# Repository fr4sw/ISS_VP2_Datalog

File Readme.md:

# ISS\_VP2\_Datalog

# Readme

Version : 0.1.6c Date : 2026-08-13

Rédacteur : Rémi Chapdelaine

# 1. Objectif du projet

Le projet ISS\_VP2\_Datalog a pour but de fournir un datalogger externe aux stations Davis Vantage Pro2 ET transmettre les informations par un lien meshtastic (ou tout autre modem série).

Ce projet a vocation a utiliser directement l'ISS (ensemble de capteurs) sans nécessiter la console et le module datalogger de Davis, permettant des économies.

L'horodatage fiable fait partie des principes important pour pouvoir recoller les informations des différentes stations.

La normalisation des unités et des mesures doit viser les bonnes pratiques en météorologie, dans les limites de ce qui est fourni par Davis.
## 1A. Etat actuel (13/8/2026 v0.1.6c)

En cours de mise au point, fonctionnel avec ISS filaire (seul temp et Hum testés), nRF52840-Xiao, BME680, RTC DS3231, GPS, carte µSD.
Certains paramétrage peuvent s'effectuer depuis le moniteur série (serial).
Sur la carte SD on écrit toutes les 30s (paramétrable) dans un fichier .csv; toutes les 5 minutes (paramétrable) on fait la synthèse (comme le fait WeeWx/Davis...) et on enregistre aussi (c'est cela qu'on enverra).

On écrit aussi un EVENTS.log qui récapitule les évènements principaux (dont les durée d'allumage GPS et les décalages horaires - permettront d'estimer la possibilité d'allonger la durée de recalage).

Meshtastic en protobuff simplifié est globalement validé, les infos remontent, tests à poursuivre.

En cours : automatisation du capteur I2C interne pour supporter/reconaitre automatiquement BME680, BME280, BMP280 ...

# 2. Contexte
Ce projet a été utilisé plusieurs années comme projet de fin d'étude en BTS Systèmes numériques/CIEL Electronique en partenariat avec l'association MeteoR-OI.

# 3. Pré-requis - versions
Testé :
IDE/Core : Arduino IDE portable 1.8.19, core Seed nRF52 Boards 1.1.13, core ESP32 3.2.0-\>3.3.11 (Wire et SD sont utilisés mais elles sont incluses dans les Cores)
Librairies : 
- BME680 Adafruit (2.0.6) (Adafruit BusIO 1.17.4, Adafruit unified sensors 1.1.15) https://github.com/adafruit/Adafruit_BME680
- RTClib Adafruit (2.1.4) https://github.com/adafruit/RTClib
- TinyGPSplus mikalhart (1.0.3) (utile seulement si GPS - Cf config/boardConfig) https://github.com/mikalhart/TinyGPSPlus

# 4. Matériel Davis

Ce projet est conçu pour récupérer les informations d'une ensemble de capteurs ISS Davis Vantage Pro2 qui existe sous 2 formes :

- filaire= liaison RS485, alimentation par le fil

- sans fil = liaison radio en modulation FSK, fréquence selon les normes locales ISM (868, 915, 433 MHz)

## 4A. Documentations
- Wiki du projet DavisRFM69, décrit les trames entre ISS et console : https://github.com/dekay/DavisRFM69/wiki/Message-Protocol
- Documentation Davis de la communication avec le Datalogger (weatherlink) : https://support.davisinstruments.com/article/rbzgl0rh6k-vantage-pro-pro-2-and-vue-communications-reference-2-6-1-any-os pointe vers https://cdn.shopify.com/s/files/1/0515/5992/3873/files/VantageSerialProtocolDocs_v261.pdf?v=1614399559
  
- Meteoengins décrit la méthode d'enregistrement dans Weatherlink et datalogger ainsi que les calculs de données dérivées (indice de chaleur, point de rosée, évapotranspiration, ...) : http://meteoengins.fr/documents/davis/Davis_Data_Archived_v3.pdf

# 5. Matériel

Des cartes spécifiques ont été conçues par les étudiants de BTS durant les projets ou par l'enseignant, cf rubrique Hardware.

Le logiciel utilisé est Kicad 9.

# 6. Logiciel

Le logiciel est structuré pour permettre :

- des développements partagés (modules par fonction)

- une maintenance facile (commentaires, documentation)

- un développement sur des matériels différents (couches d'abstraction, définitions des cartes et pins centralisées)

- Arduino 1.8.19 portable ou PlatformIO, les 2 peuvent etre utilisés

Les développements doivent respecter les règles de codage (cf doc) et etre accessible à des BTS.  
Chaque ligne de code doit pouvoir être expliquée à un étudiant de BTS.  
Si une ligne nécessite une longue explication, elle doit être réécrite de manière plus explicite.

Une partie du développement a été réalisé avec l'aide de Claude Sonnet 5, en corrigeant ses erreurs et affinant les possibiités.

Les règles de codages sont dans le document CodingRules.md

# 7. Gestion de l'alimentation

La cible visée étant l'autonomie totale (énergétique et réseau) la préservation de l'énergie devra etre incluse dans les réflexions.

L'usage de panneaux photovoltaique et de batteries ou super condensateurs est quasi indispensable et sera à optimiser.

Cette partie n'a pas encore été détaillée.

# 8. A venir

Cf ToDo list et issues pour les détails

Augmenter/tester les capteurs de pression (et autres mesures) intégrables (BME280, DHT, ...) et automatiser (le BME680 est déjà intégré) pour disposer de la température interne et de la pression atmosphérique (éléments qui étaient fournis par la console et non par l'ISS).

Calibration des différentes données (température, humidité, pression) et stockage des paramètres de calibration

# 9. ?

?

# Photos

.

.

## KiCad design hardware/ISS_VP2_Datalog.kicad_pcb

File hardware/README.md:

# MeteoRoi\_2026\_VP2\_Meshtastic

Projet BTS CIEL ER basé sur les ISS des Station Davis VantagePro2 fil ou sans fil, destiné à étendre la portée avec Meshtastic(série) et contenir datalogger, SD, GPS, RTC.

# STATUT

Première version reçue et partiellement testé (cf issues) (30/6/2026)

Pas encore réalisé ni testé - en attente de livraison du PCB et des composants (26 mai 2026).

# Outils\_Logiciels

Kicad 9.0.9 a été utilisé.

# Auteurs

le PCB a été conçu par l'enseignant M.Chapdelaine, faute de conception dans les temps par les étudiants.

# Micro-controleur

Pour des raisons d'économie d'énergie le choix s'est porté sur un nRF52840, largement utilisé dans les répéteurs autonomes meshtastic pour sa faible consommation  Le modele SeedStudio xiao standard a été choisi

# Périphériques

l'UART est multiplexée par un commutateur analogique :  

- le GPS n'est utilisé qu'une fois par jour pour récupérer l'heure exacte, durant ce temps on peut ne pas émettre en Meshtastic

Le RTC a été dupliqué sous forme de Pins pour insérer un module car les chip DS3231M se sont avérés etre des Fakes et le cout d'un module est inférieur au cout du chip !

## Internes

I2C :

> SDA : P1.12 SCL : P1.13

RTC : DS3231M - I2C - ?  Pression (et température, humidité interne) : Carte BMP680 - I2C - 0x77   SPI (le port 0 est plus rapide): 

> SCK = P0.02 MOSI = P0.03 MISO = P0.28

µSD : SPI, CS = P0.29   RS485 : Lien avec ISS filaire - UART (Rx seulement), toute les 2,5s ou un peu plus selon le numéro d'ISS  Rx sur P0.04 (le port 0 permet des interruptions) RFM95W (SX12xx) : SPI (pour ISS sans fil) (risque d'interférence avec le Meshtastic (même bande, mais pas même modulation)  le CS utilise le meme port que la réception RS485 (soit on est en filaire, soit en sans fil) On peuple soit R8 soit R10, on peut effectuer une détection en se mettant en réception et en regardant si on reçoit l'ISS (toutes les 2,5s), ou en mesurant si on reçoit le pull-up R9 (plus douteux)

## Externes

GPS : quelconque : UART (seulement Tx vers Rx µC)  Meshtastic : Quelconque : UART  RX = P1.15 (utilisé pour GPS ou Meshtastic) Tx = P1.14 (utilisé seulement pour Meshtastic

## Multiplexage UART

Le GPS et Meshtastic partagent l'UART, la sélection s'effectue par Mesh\_EN

# Commandes alimentation

Les plus gros consommateurs peuvent etre activés à la demande (actif 0)   
GPS\_EN : P0.05   
Meshtastic\_EN : P1.11

# Alimentation Batterie/USB

Le Xiao simple ne permet pas une gestion fine de plusieurs alimentations et ne dispose que d'une entrée alimentation (différente de 3,3V) partagée avec l'alimentation USB, un cavalier a été prévu pour éviter les drames lors de l'utilisation d'une allimentation externe (batterie), ce cavalier est à enlever IMPERATIVEMENT avant branchement sur USB, sous peine de destruction/explosion du port USB et/ou de la batterie

Ce cavalier est nécessaire pour alimenter le meshtastic en l'absence de batterie.

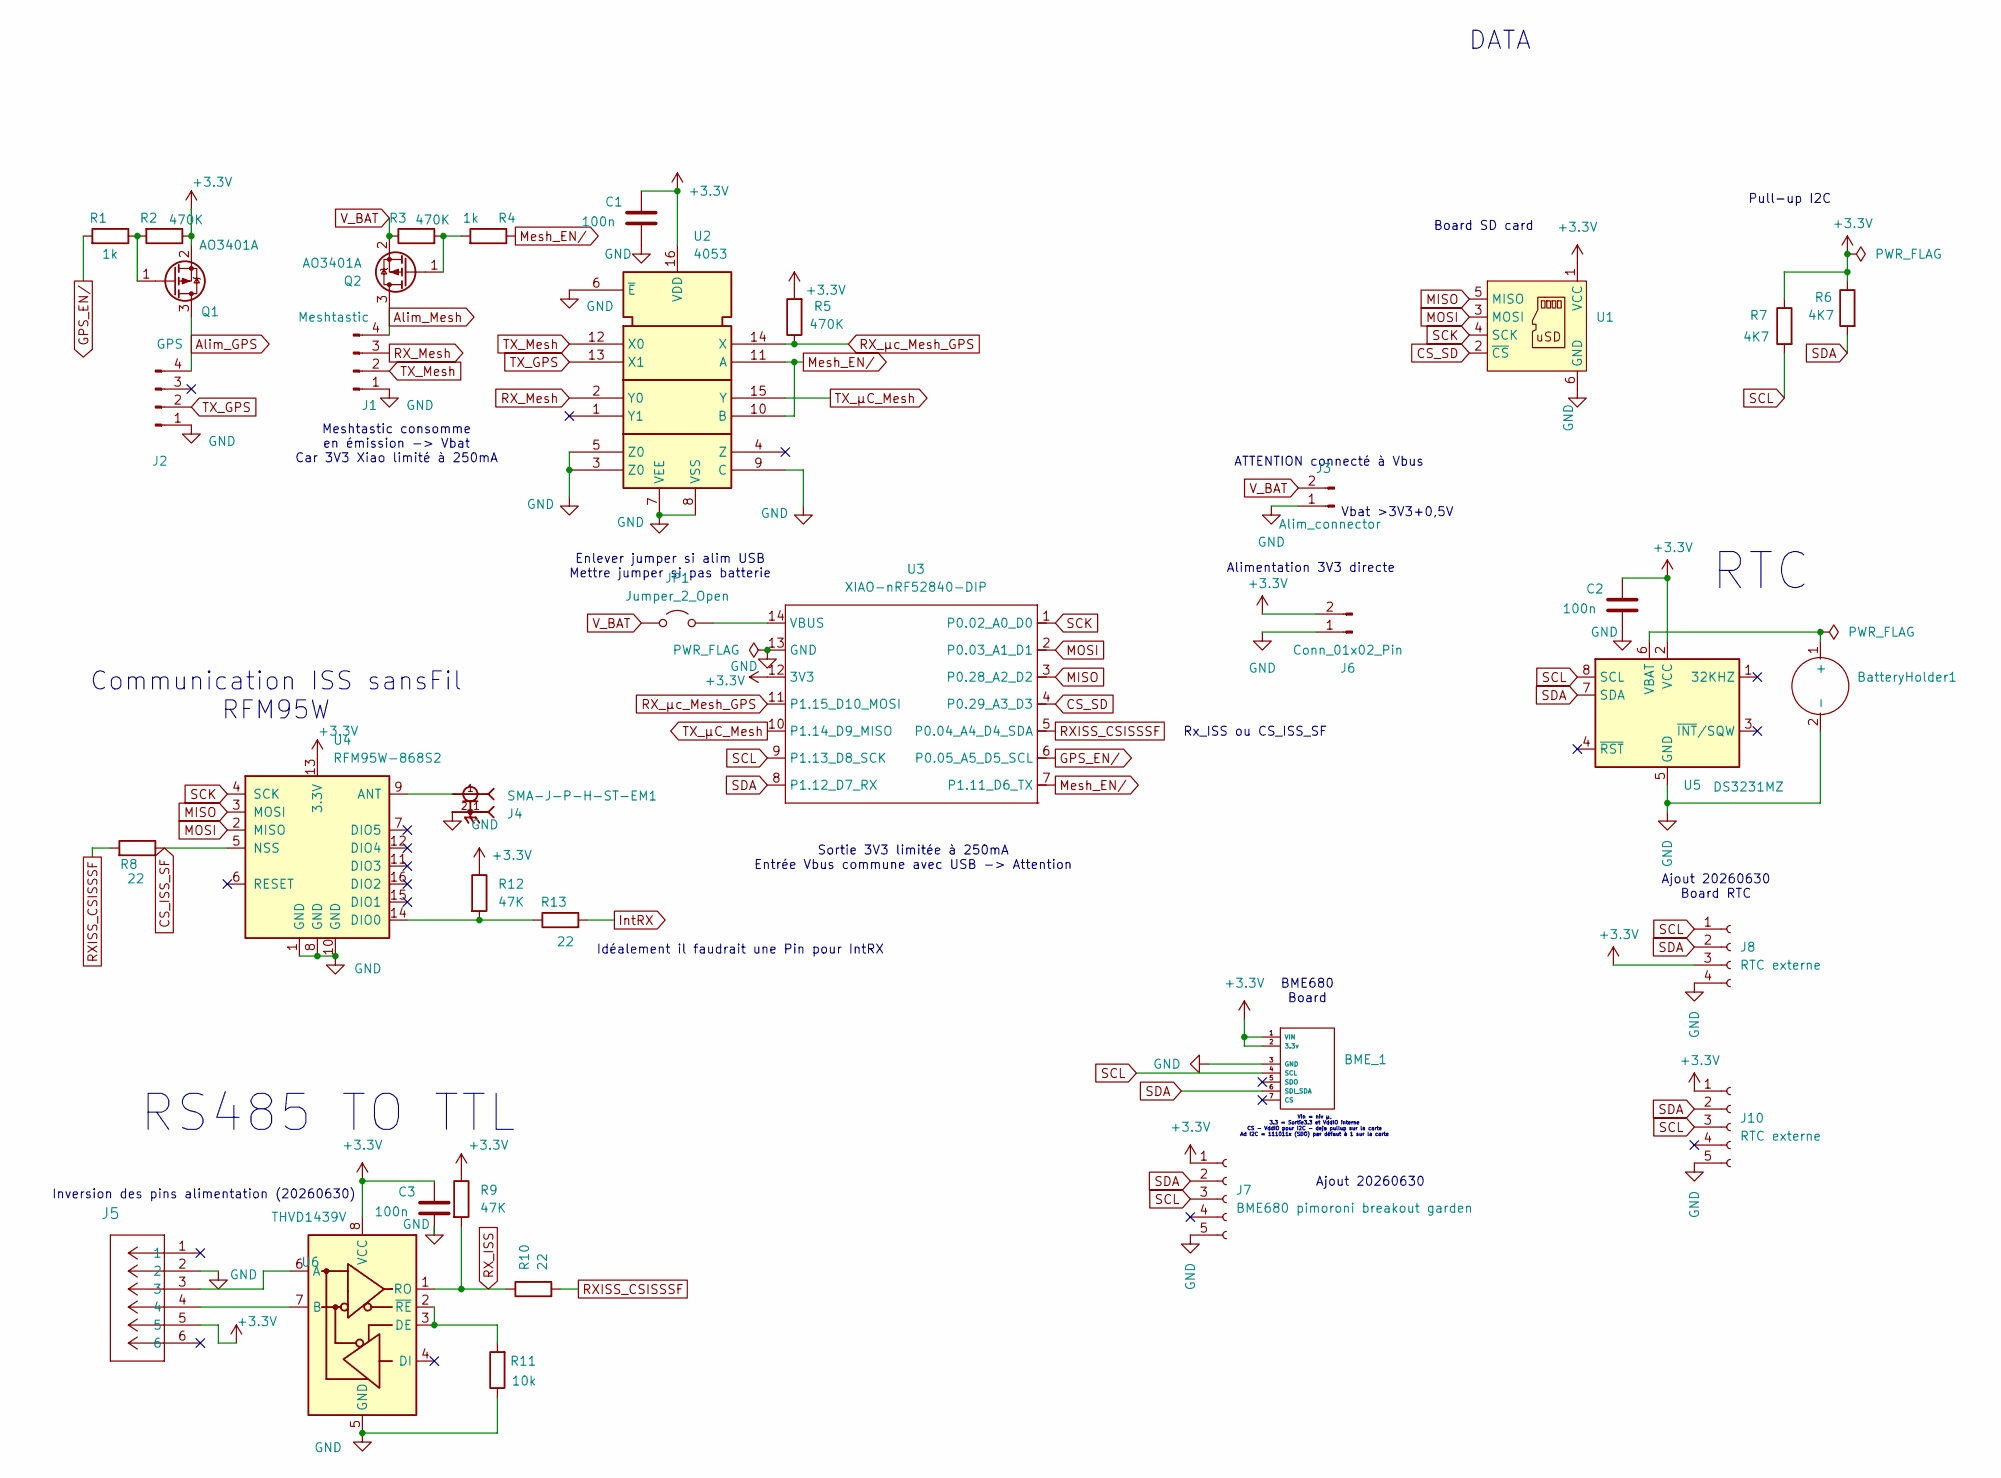
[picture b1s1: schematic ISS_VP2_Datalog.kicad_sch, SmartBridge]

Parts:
BME_1: BME680; MPN 3660
BatteryHolder1: BatteryHolder_MYOUNG_BS-07-A1BJ001_CR2032; MPN 103
C1: 100n; C_Disc_D4.7mm_W2.5mm_P5.00mm; MPN K104K15X7RF5TH5
C2, C3: 100n; C_1206_3216Metric_Pad1.33x1.80mm_HandSolder; MPN ECE-A1AN101X
J1: Meshtastic; PinHeader_1x04_P2.54mm_Vertical
J2: GPS; PinHeader_1x04_P2.54mm_Vertical
J3: Alim_connector; JST_PH_S2B-PH-K_1x02_P2.00mm_Horizontal
J4: SMA-J-P-H-ST-EM1; SAMTEC_SMA-J-P-H-ST-EM1; PARTREV G
J5: E5566-Q0LK22-L; RJ_CONN6_E5566_PUL
J6: Conn_01x02_Pin; PinHeader_1x02_P2.54mm_Vertical
J7: BME680 pimoroni breakout garden; PinSocket_1x05_P2.54mm_Vertical
J8: RTC externe; PinSocket_1x04_P2.54mm_Vertical
J10: RTC externe; PinSocket_1x05_P2.54mm_Vertical
JP1: Jumper_2_Open; PinHeader_1x02_P2.54mm_Vertical
Q1, Q2: AO3401A; SOT-23; MPN CF14JT1K00
R1, R4: 1k; R_1206_3216Metric_Pad1.30x1.75mm_HandSolder; MPN CF14JT1K00
R2: 470K; R_1206_3216Metric_Pad1.30x1.75mm_HandSolder
R3: 470K; R_1206_3216Metric_Pad1.30x1.75mm_HandSolder; MPN PCF1C473K
R5: 470K; R_Axial_DIN0207_L6.3mm_D2.5mm_P2.54mm_Vertical; MPN MF25 470K
R6, R7: 4K7; R_Axial_DIN0207_L6.3mm_D2.5mm_P2.54mm_Vertical; MPN MFR-25FRF52-1K
R8, R10: 22; R_Axial_DIN0207_L6.3mm_D2.5mm_P7.62mm_Horizontal; MPN MFR-25FTE52-22R
R9, R12: 47K; R_1206_3216Metric_Pad1.30x1.75mm_HandSolder; MPN RC1206FR-0747KL
R11: 10k; R_Axial_DIN0207_L6.3mm_D2.5mm_P2.54mm_Vertical; MPN MFR-25FRF52-10K
R13: 22; R_Axial_DIN0207_L6.3mm_D2.5mm_P2.54mm_Vertical; MPN MFR-25FTE52-22R
U1: MicroSD-Adapter
U2: 4053; DIP-16_W7.62mm_LongPads
U3: XIAO-nRF52840-DIP
U4: RFM95W-868S2; HOPERF_RFM9XW_THT
U5: DS3231MZ; SOIC-8_3.9x4.9mm_P1.27mm; MPN DS3231MZ+TRL
U6: THVD1439V; SOIC-8_3.9x4.9mm_P1.27mm; MPN THVD1439DR

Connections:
+3.3V: BME_1.1 (VIN), BME_1.2 (3.3v), C1.1, C2.1, C3.1, J5.5, J6.2, J7.1, J8.3, J10.1, Q1.2 (S), R2.1, R5.2, R6.1, R7.1, R9.1, R12.1, U1.1 (VCC), U2.16 (VDD), U3.12 (3V3), U4.13 (3.3V), U5.2 (VCC), U6.8 (VCC)
Alim_GPS: J2.4, Q1.3 (D)
Alim_Mesh: J1.4, Q2.3 (D)
CS_ISS_SF: R8.1, U4.5 (NSS)
CS_SD: U1.2 (~CS), U3.4 (P0.29_A3_D3)
GND: BME_1.3 (GND), BatteryHolder1.2 (-), C1.2, C2.2, C3.2, J1.1, J2.1, J3.1, J4.2_1, J4.2_2, J4.3_1, J4.3_2, J5.2, J6.1, J7.5, J8.4, J10.5, R11.1, U1.6 (GND), U2.3 (Z0), U2.5 (Z0), U2.6 (~E), U2.7 (VEE), U2.8 (VSS), U2.9 (C), U3.13 (GND), U4.1 (GND), U4.8 (GND), U4.10 (GND), U5.5 (GND), U6.5 (GND)
GPS_EN/: R1.2, U3.6 (P0.05_A5_D5_SCL)
IntRX: R13.2
MISO: U1.5 (MISO), U3.3 (P0.28_A2_D2), U4.3 (MOSI)
MOSI: U1.3 (MOSI), U3.2 (P0.03_A1_D1), U4.2 (MISO)
Mesh_EN/: R4.1, U2.10 (B), U2.11 (A), U3.7 (P1.11_D6_TX)
unnamed: BatteryHolder1.1 (+), U5.6 (VBAT)
unnamed: JP1.2 (B), U3.14 (VBUS)
unnamed: Q1.1 (G), R1.1, R2.2
unnamed: Q2.1 (G), R3.2, R4.2
unnamed: J4.1, U4.9 (ANT)
unnamed: R12.2, R13.1, U4.14 (DIO0)
unnamed: J5.3, U6.6 (A)
unnamed: J5.4, U6.7 (B)
unnamed: R11.2, U6.2 (~RE), U6.3 (DE)
RXISS_CSISSSF: R8.2, R10.2, U3.5 (P0.04_A4_D4_SDA)
RX_ISS: R9.2, R10.1, U6.1 (RO)
RX_Mesh: J1.3, U2.2 (Y0)
RX_µc_Mesh_GPS: R5.1, U2.14 (X), U3.11 (P1.15_D10_MOSI)
SCK: U1.4 (SCK), U3.1 (P0.02_A0_D0), U4.4 (SCK)
SCL: BME_1.4 (SCL), J7.3, J8.1, J10.3, R7.2, U3.9 (P1.13_D8_SCK), U5.8 (SCL)
SDA: BME_1.6 (SDI_SDA), J7.2, J8.2, J10.2, R6.2, U3.8 (P1.12_D7_RX), U5.7 (SDA)
TX_GPS: J2.2, U2.13 (X1)
TX_Mesh: J1.2, U2.12 (X0)
TX_µC_Mesh: U2.15 (Y), U3.10 (P1.14_D9_MISO)
V_BAT: J3.2, JP1.1 (A), Q2.2 (S), R3.1

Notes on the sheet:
Vbat >3V3+0,5V
Sortie 3V3 limitée à 250mA Entrée Vbus commune avec USB -> Attention
Alimentation 3V3 directe
BME680 Board
DATA
ATTENTION connecté à Vbus
Ajout 20260630
Ajout 20260630 Board RTC
Board SD card
RS485 TO TTL
RTC
Vin = niv µ, 3.3 = Sortie3.3 et VddIO interne CS - VddIO pour I2C - deja pullup sur la carte Ad I2C = 111011x (SDO) par défaut à 1 sur la carte
Enlever jumper si alim USB Mettre jumper si pas batterie
Meshtastic consomme en émission -> Vbat Car 3V3 Xiao limité à 250mA
Inversion des pins alimentation (20260630)
Pull-up I2C
Rx_ISS ou CS_ISS_SF
Idéalement il faudrait une Pin pour IntRX
Communication ISS sansFil RFM95W

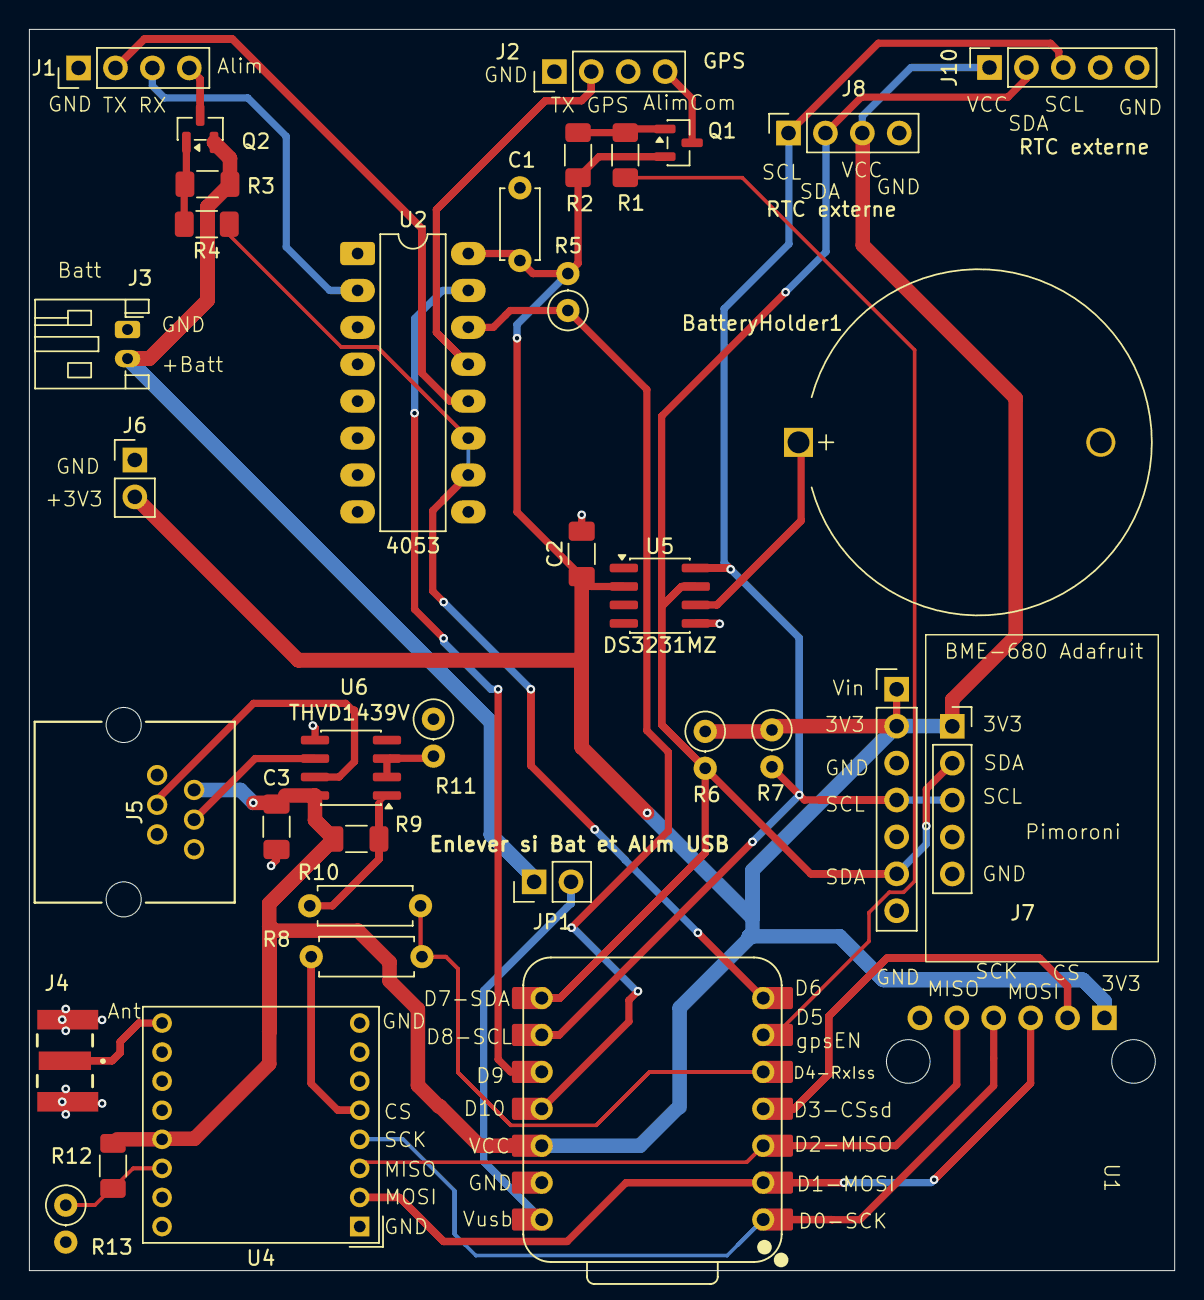
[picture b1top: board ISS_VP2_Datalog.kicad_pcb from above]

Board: 2 copper layers, 78.8 x 85.4 mm, 36 parts (0 on the bottom side), 30 nets.
